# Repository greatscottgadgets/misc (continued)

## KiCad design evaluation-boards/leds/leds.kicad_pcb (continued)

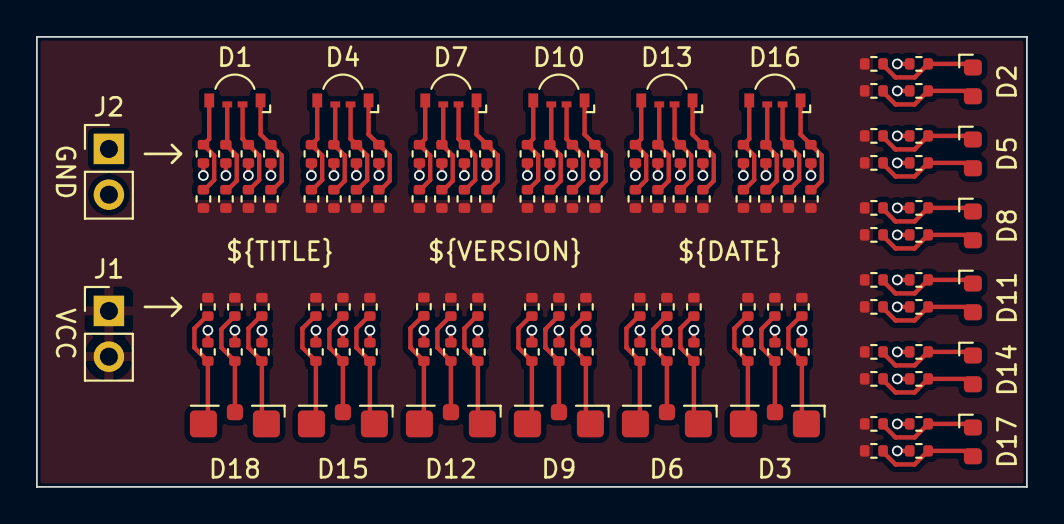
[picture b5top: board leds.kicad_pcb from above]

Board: 2 copper layers, 55.0 x 25.0 mm, 128 parts (0 on the bottom side), 56 nets.

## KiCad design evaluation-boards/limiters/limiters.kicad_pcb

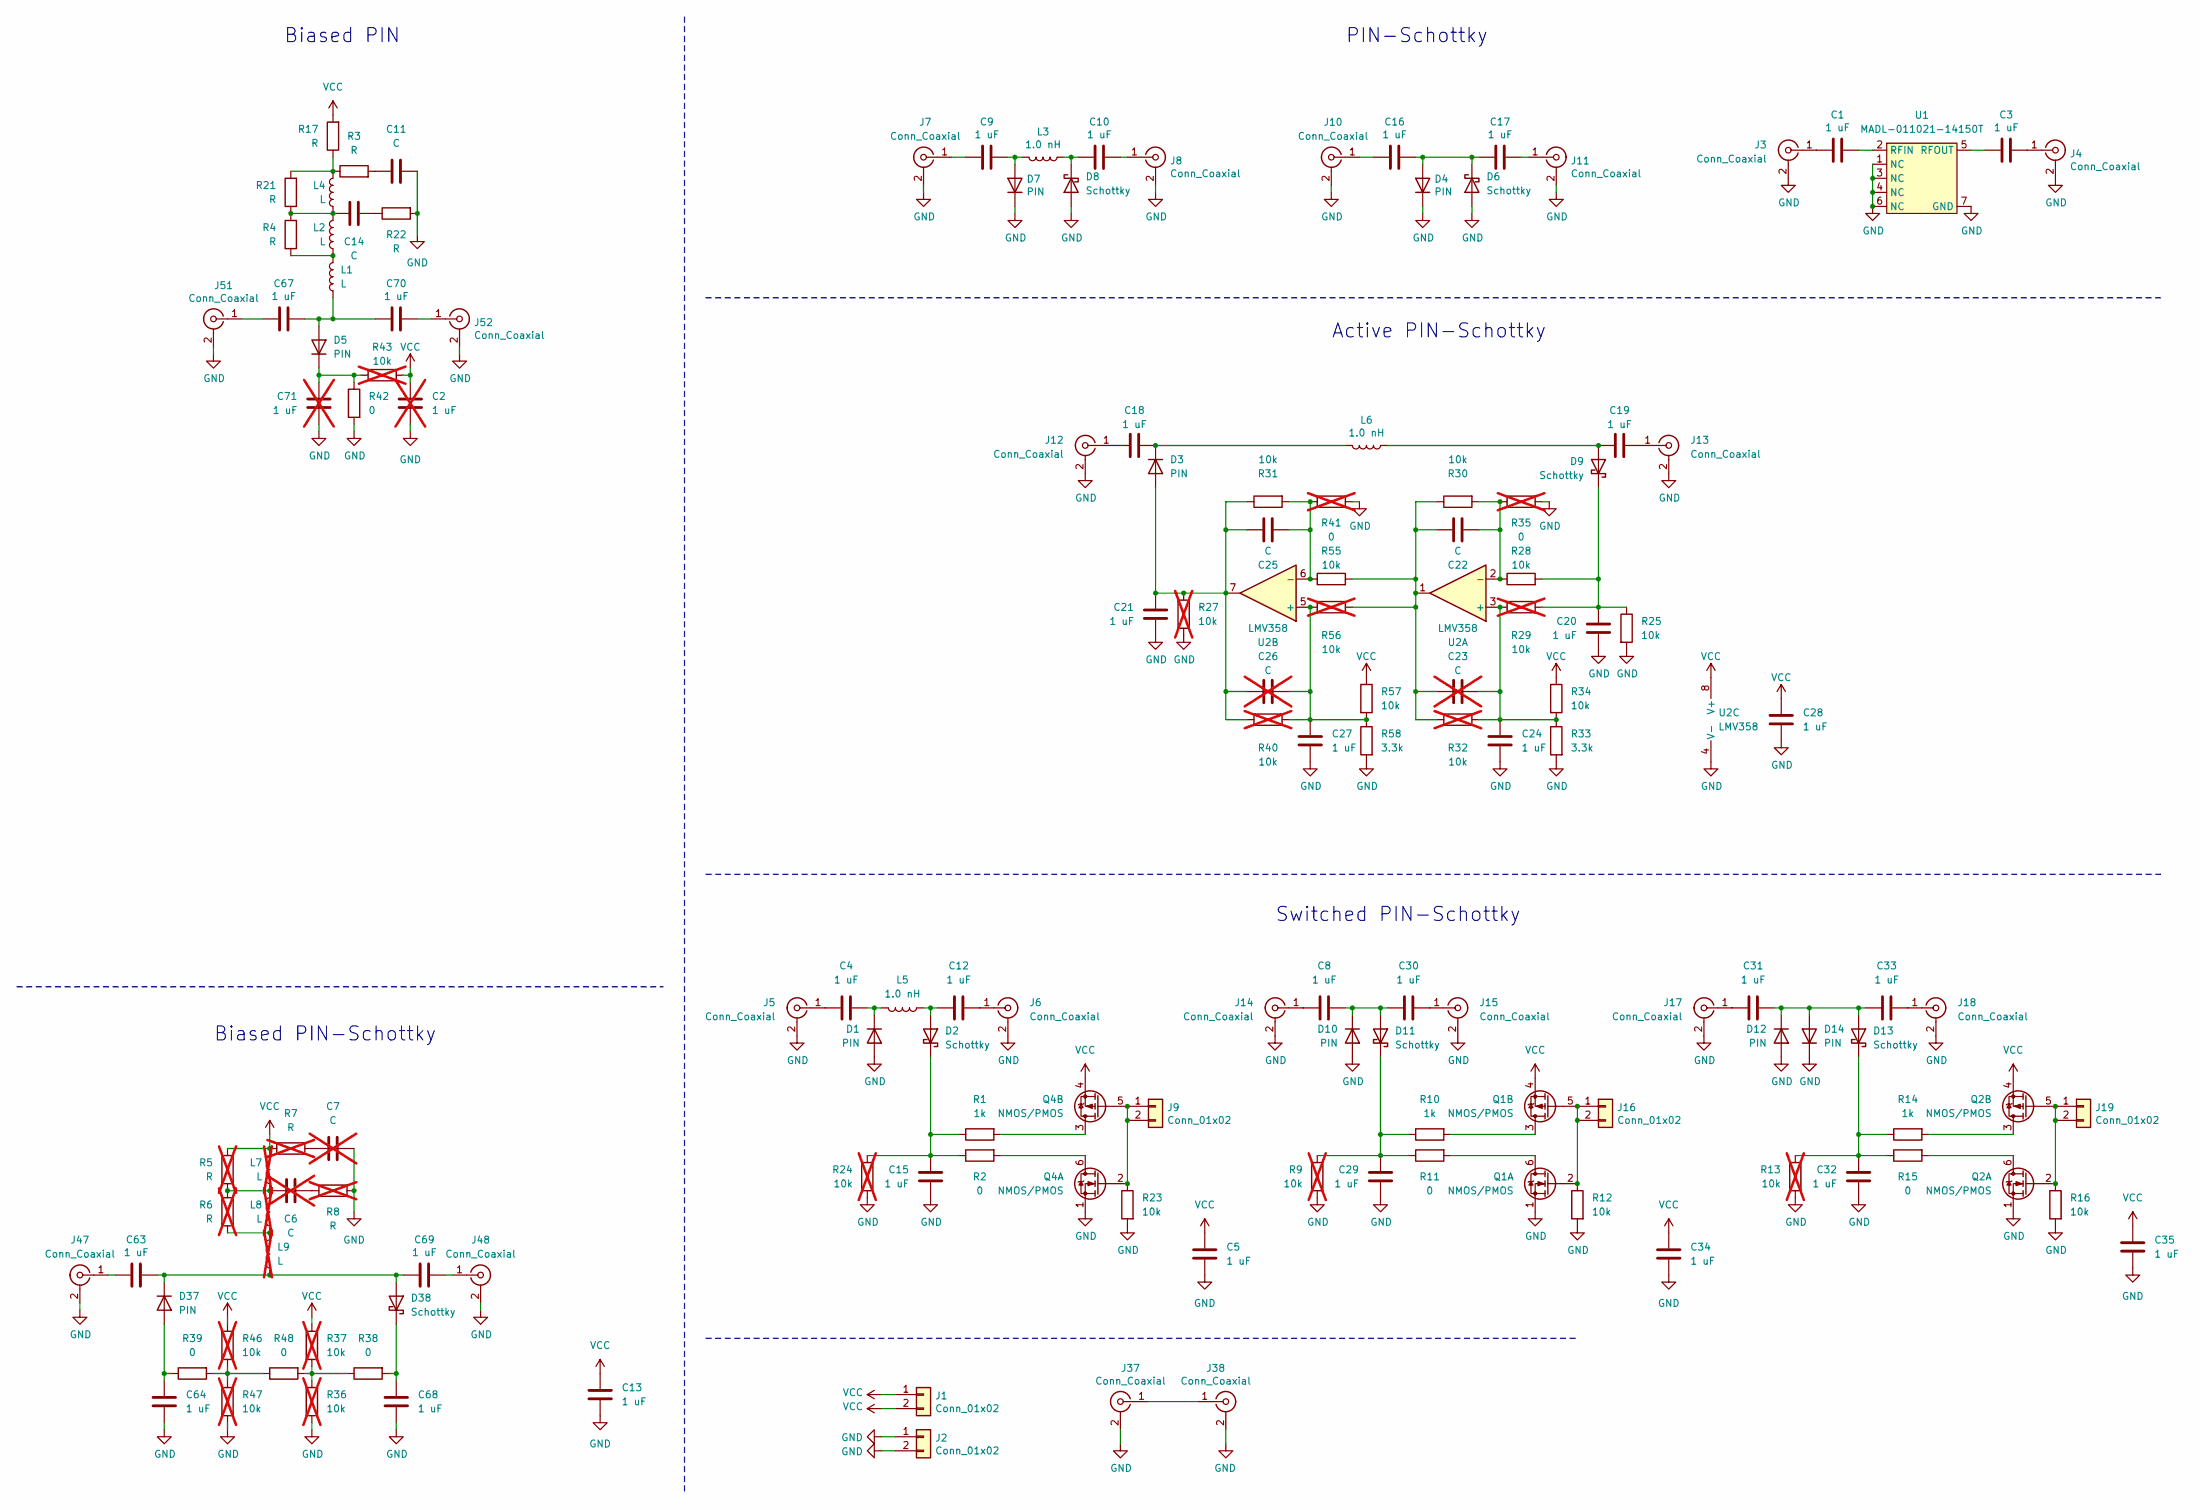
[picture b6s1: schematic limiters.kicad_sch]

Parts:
C1, C3, C5, C10, C12, C13, C15, C17, C18, C19, C20, C21, C24, C27, C28, C29, C30, C32, C33, C34, C35, C63, C64, C67, C68, C69, C70: 1 uF; C_0201_0603Metric; Part Number GRM033R61A105ME44D
C2, C71: 1 uF; C_0201_0603Metric; Part Number GRM033R61A105ME44D; not fitted
C4, C8, C31: 1 uF; C_0402_1005Metric; Part Number Capacitor_SMD:C_0402_1005Metric
C6, C7, C23, C26: C; C_0201_0603Metric; not fitted
C9, C16: 1 uF; C_0402_1005Metric
C11, C14, C22, C25: C; C_0201_0603Metric
D1, D3, D4, D5, D7, D10, D12, D14, D37: PIN; TSLP-2-19; Part Number BAR9002ELE6327XTMA1
D2, D6, D8, D9, D11, D13, D38: Schottky; TSSLP-2-1; Part Number BAT2402LSE6327XTSA1
J1, J2, J9, J16, J19: Conn_01x02; PinHeader_1x02_P2.54mm_Vertical
J3, J4, J5, J6, J7, J8, J10, J11, J12, J13, J14, J15, J17, J18, J37, J38, J47, J48, J51, J52: Conn_Coaxial; Linx_SMA_CONSMA003.062; Part Number CONSMA003.062
L1, L2: L; L_0201_0603Metric
L3, L5, L6: 1.0 nH; L_0201_0603Metric; Part Number LQP03HQ1N0W02D
L4: L; L_0805_2012Metric
L7: L; L_0805_2012Metric; not fitted
L8, L9: L; L_0201_0603Metric; not fitted
Q1, Q2, Q4: NMOS/PMOS; SOT-563; Part Number DMC2400UV
R1, R10, R14: 1k; R_0402_1005Metric
R2, R11, R15, R38, R39, R42, R48: 0; R_0402_1005Metric
R3, R4, R17, R21, R22: R; R_0201_0603Metric
R5, R6, R7, R8: R; R_0201_0603Metric; not fitted
R9, R13, R24, R27, R29, R32, R36, R37, R40, R43, R46, R47, R56: 10k; R_0402_1005Metric; not fitted
R12, R16, R23, R25, R28, R30, R31, R34, R55, R57: 10k; R_0402_1005Metric
R33, R58: 3.3k; R_0402_1005Metric
R35, R41: 0; R_0402_1005Metric; not fitted
U1: MADL-011021-14150T; TDFN-6-1EP_1.5x1.2mm_P0.4mm_EP0.47x0.8mm
U2: LMV358; MSOP-8_3x3mm_P0.65mm

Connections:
GND: C2.2, C5.2, C7.1, C11.1, C13.2, C15.2, C20.2, C21.2, C24.2, C27.2, C28.2, C29.2, C32.2, C34.2, C35.2, C64.2, C68.2, C71.2, D1.2 (A), D4.1 (K), D6.2 (A), D7.1 (K), D8.2 (A), D10.2 (A), D12.2 (A), D14.1 (K), J2.1, J2.2, J3.2 (Ext), J4.2 (Ext), J5.2 (Ext), J6.2 (Ext), J7.2 (Ext), J8.2 (Ext), J10.2 (Ext), J11.2 (Ext), J12.2 (Ext), J13.2 (Ext), J14.2 (Ext), J15.2 (Ext), J17.2 (Ext), J18.2 (Ext), J37.2 (Ext), J38.2 (Ext), J47.2 (Ext), J48.2 (Ext), J51.2 (Ext), J52.2 (Ext), Q1.1 (S), Q2.1 (S), Q4.1 (S), R8.2, R9.2, R12.2, R13.2, R16.2, R22.2, R23.2, R24.2, R25.2, R27.2, R33.2, R35.2, R36.2, R41.2, R42.2, R47.2, R58.2, U1.1 (NC), U1.3 (NC), U1.4 (NC), U1.6 (NC), U1.7 (GND), U2.4 (V-)
unnamed: C6.1, R8.1
unnamed: C6.2, L7.1, L8.2, R5.1, R6.2
unnamed: C7.2, R7.2
unnamed: C11.2, R3.2
unnamed: C14.1, R22.1
unnamed: C14.2, L2.2, L4.1, R4.2, R21.1
unnamed: C22.1, C23.1, R30.1, R32.1, R55.2, R56.2, U2.1
unnamed: C4.1, D1.1 (K), L5.2
unnamed: C12.2, D2.2 (A), L5.1
unnamed: C15.1, D2.1 (K), R1.1, R2.1, R24.1
unnamed: C21.1, C25.1, C26.1, D3.2 (A), R27.1, R31.1, R40.1, U2.7
unnamed: C18.1, D3.1 (K), L6.2
unnamed: C16.1, C17.2, D4.2 (A), D6.1 (K)
unnamed: C67.1, C70.2, D5.2 (A), L1.1
unnamed: C71.1, D5.1 (K), R42.1, R43.1
unnamed: C9.1, D7.2 (A), L3.2
unnamed: C10.2, D8.1 (K), L3.1
unnamed: C19.2, D9.2 (A), L6.1
unnamed: C20.1, D9.1 (K), R25.1, R28.2, R29.2
unnamed: C8.1, C30.2, D10.1 (K), D11.2 (A)
unnamed: C29.1, D11.1 (K), R9.1, R10.1, R11.1
unnamed: C31.1, C33.2, D12.1 (K), D13.2 (A), D14.2 (A)
unnamed: C32.1, D13.1 (K), R13.1, R14.1, R15.1
unnamed: C64.1, D37.2 (A), R39.1
unnamed: C63.1, C69.2, D37.1 (K), D38.2 (A), L9.1
unnamed: C68.1, D38.1 (K), R38.2
unnamed: C1.2, J3.1 (In)
unnamed: C3.1, J4.1 (In)
unnamed: C4.2, J5.1 (In)
unnamed: C12.1, J6.1 (In)
unnamed: C9.2, J7.1 (In)
unnamed: C10.1, J8.1 (In)
unnamed: J9.1, J9.2, Q4.2 (G), Q4.5 (G), R23.1
unnamed: C16.2, J10.1 (In)
unnamed: C17.1, J11.1 (In)
unnamed: C18.2, J12.1 (In)
unnamed: C19.1, J13.1 (In)
unnamed: C8.2, J14.1 (In)
unnamed: C30.1, J15.1 (In)
unnamed: J16.1, J16.2, Q1.2 (G), Q1.5 (G), R12.1
unnamed: C31.2, J17.1 (In)
unnamed: C33.1, J18.1 (In)
unnamed: J19.1, J19.2, Q2.2 (G), Q2.5 (G), R16.1
unnamed: J37.1 (In), J38.1 (In)
unnamed: C63.2, J47.1 (In)
unnamed: C69.1, J48.1 (In)
unnamed: C67.2, J51.1 (In)
unnamed: C70.1, J52.1 (In)
unnamed: L1.2, L2.1, R4.1
unnamed: L4.2, R3.1, R17.1, R21.2
unnamed: L8.1, L9.2, R6.1
unnamed: Q1.6 (D), R11.2
unnamed: Q1.3 (D), R10.2
unnamed: Q2.6 (D), R15.2
unnamed: Q2.3 (D), R14.2
unnamed: Q4.6 (D), R2.2
unnamed: Q4.3 (D), R1.2
unnamed: R36.1, R37.2, R38.1, R48.2
unnamed: R39.2, R46.2, R47.1, R48.1
unnamed: C1.1, U1.2 (RFIN)
unnamed: C3.2, U1.5 (RFOUT)
unnamed: C23.2, C24.1, R29.1, R32.2, R33.1, R34.2, U2.3 (+)
unnamed: C22.2, R28.1, R30.2, R35.1, U2.2 (-)
unnamed: C26.2, C27.1, R40.2, R56.1, R57.2, R58.1, U2.5 (+)
unnamed: C25.2, R31.2, R41.1, R55.1, U2.6 (-)
VCC: C2.1, C5.1, C13.1, C28.1, C34.1, C35.1, J1.1, J1.2, L7.2, Q1.4 (S), Q2.4 (S), Q4.4 (S), R5.2, R7.1, R17.2, R34.1, R37.1, R43.2, R46.1, R57.1, U2.8 (V+)

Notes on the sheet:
Active PIN-Schottky
Switched PIN-Schottky
Biased PIN-Schottky
PIN-Schottky
Biased PIN

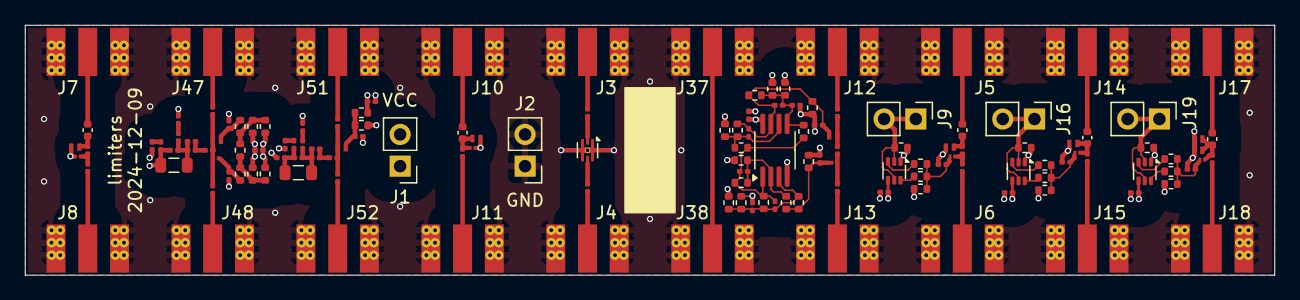
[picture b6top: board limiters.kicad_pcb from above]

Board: 4 copper layers, 100.0 x 20.0 mm, 143 parts (0 on the bottom side), 67 nets.

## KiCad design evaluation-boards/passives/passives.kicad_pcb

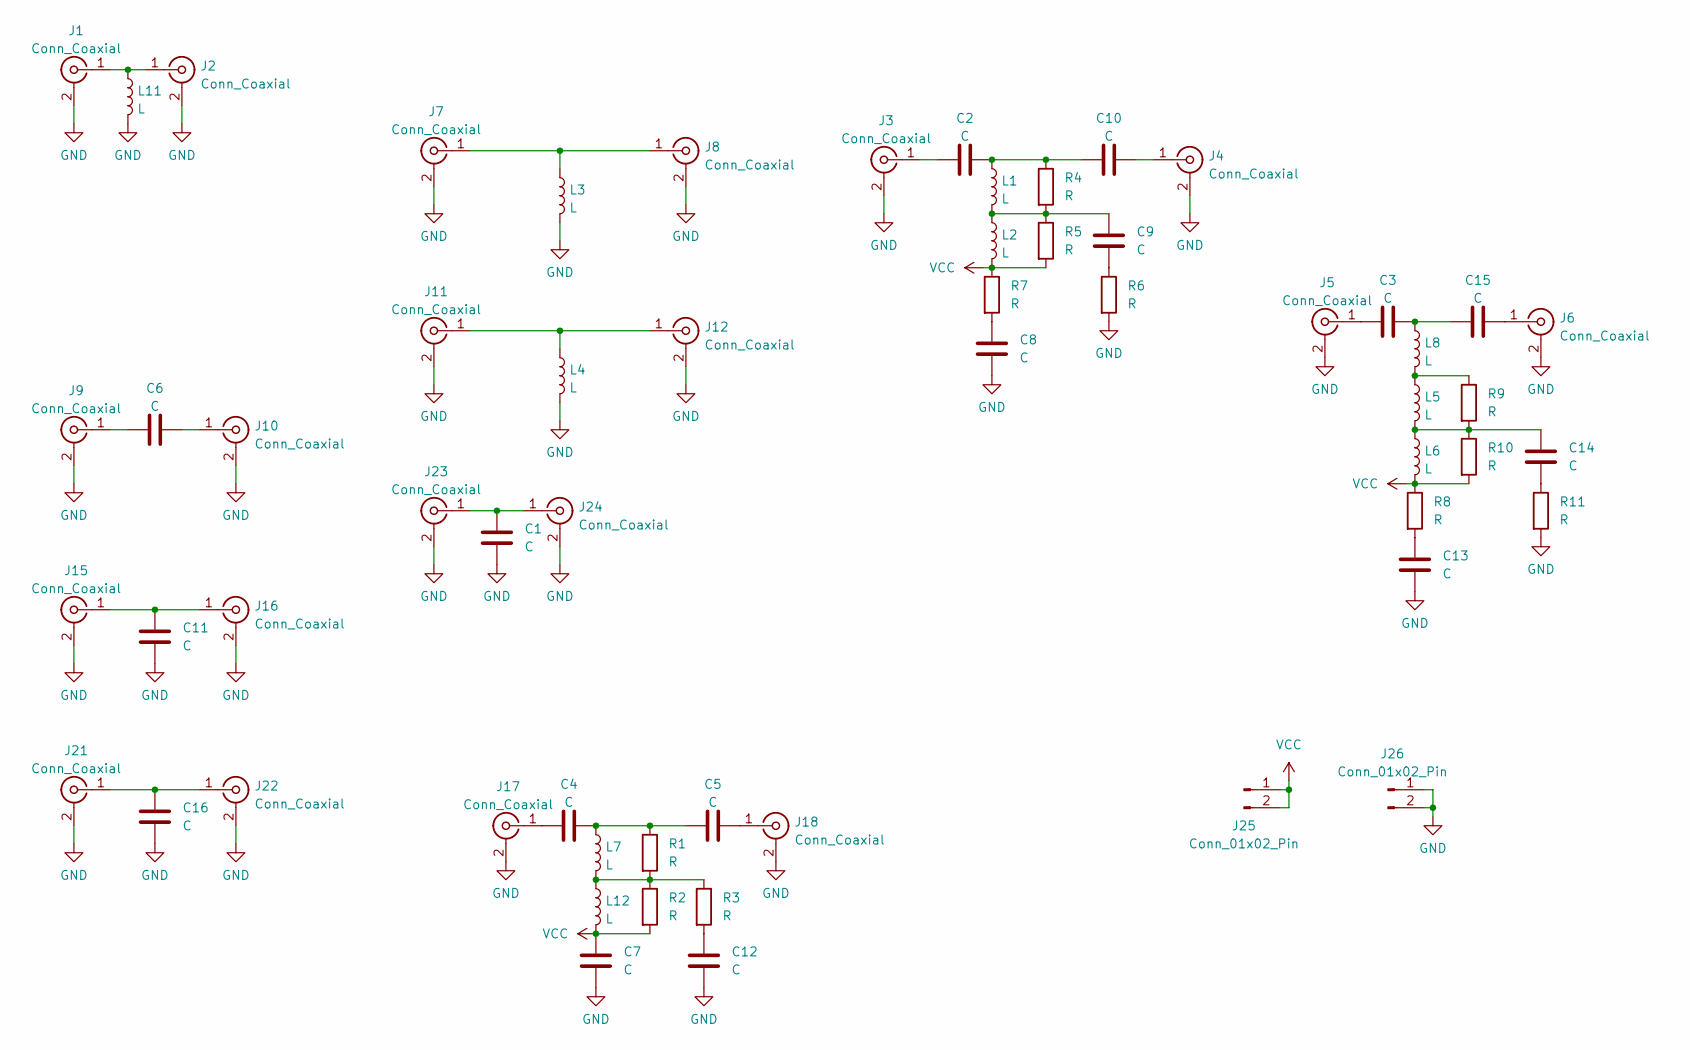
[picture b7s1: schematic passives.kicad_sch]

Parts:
C1, C2, C3, C4, C5, C8, C9, C10, C11, C13, C14, C15: C; C_0201_0603Metric
C6, C7, C12, C16: C; C_0402_1005Metric
J1, J2, J3, J4, J5, J6, J7, J8, J9, J10, J11, J12, J15, J16, J17, J18, J21, J22, J23, J24: Conn_Coaxial; Linx_SMA_CONSMA003.062
J25, J26: Conn_01x02_Pin; PinHeader_1x02_P2.54mm_Vertical
L1, L5, L8: L; L_0201_0603Metric
L2, L4, L6: L; L_0805_2012Metric
L3, L7, L11, L12: L; L_0603_1608Metric
R1, R2, R3: R; R_0402_1005Metric
R4, R5, R6, R7, R8, R9, R10, R11: R; R_0201_0603Metric

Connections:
GND: C1.1, C7.1, C8.1, C11.1, C12.1, C13.1, C16.1, J1.2 (Ext), J2.2 (Ext), J3.2 (Ext), J4.2 (Ext), J5.2 (Ext), J6.2 (Ext), J7.2 (Ext), J8.2 (Ext), J9.2 (Ext), J10.2 (Ext), J11.2 (Ext), J12.2 (Ext), J15.2 (Ext), J16.2 (Ext), J17.2 (Ext), J18.2 (Ext), J21.2 (Ext), J22.2 (Ext), J23.2 (Ext), J24.2 (Ext), J26.1, J26.2, L3.2, L4.2, L11.2, R6.2, R11.2
unnamed: C4.2, C5.1, L7.1, R1.1
unnamed: C8.2, R7.2
unnamed: C9.1, R6.1
unnamed: C9.2, L1.2, L2.1, R4.2, R5.1
unnamed: C2.2, C10.1, L1.1, R4.1
unnamed: C12.2, R3.2
unnamed: C13.2, R8.2
unnamed: C14.1, R11.1
unnamed: C14.2, L5.2, L6.1, R9.2, R10.1
unnamed: C3.2, C15.1, L8.1
unnamed: J1.1 (In), J2.1 (In), L11.1
unnamed: C2.1, J3.1 (In)
unnamed: C10.2, J4.1 (In)
unnamed: C3.1, J5.1 (In)
unnamed: C15.2, J6.1 (In)
unnamed: J7.1 (In), J8.1 (In), L3.1
unnamed: C6.1, J9.1 (In)
unnamed: C6.2, J10.1 (In)
unnamed: J11.1 (In), J12.1 (In), L4.1
unnamed: C11.2, J15.1 (In), J16.1 (In)
unnamed: C4.1, J17.1 (In)
unnamed: C5.2, J18.1 (In)
unnamed: C16.2, J21.1 (In), J22.1 (In)
unnamed: C1.2, J23.1 (In), J24.1 (In)
unnamed: L5.1, L8.2, R9.1
unnamed: L7.2, L12.1, R1.2, R2.1, R3.1
VCC: C7.2, J25.1, J25.2, L2.2, L6.2, L12.2, R2.2, R5.2, R7.1, R8.1, R10.2

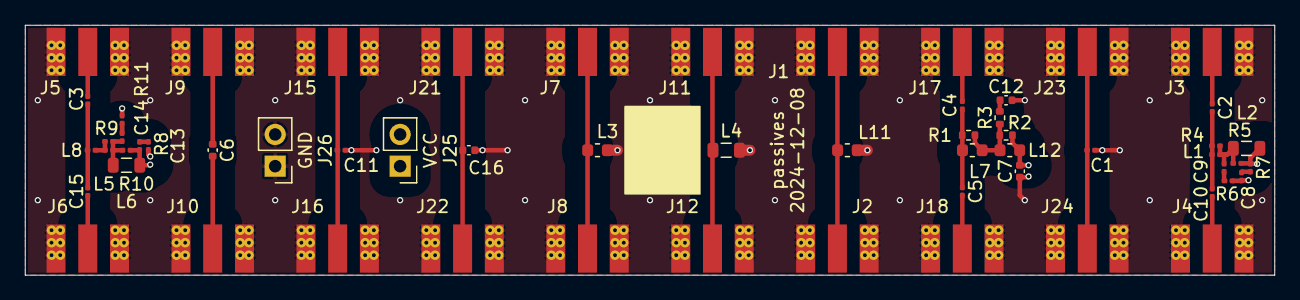
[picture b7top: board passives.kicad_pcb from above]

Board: 4 copper layers, 100.0 x 20.0 mm, 59 parts (0 on the bottom side), 28 nets.

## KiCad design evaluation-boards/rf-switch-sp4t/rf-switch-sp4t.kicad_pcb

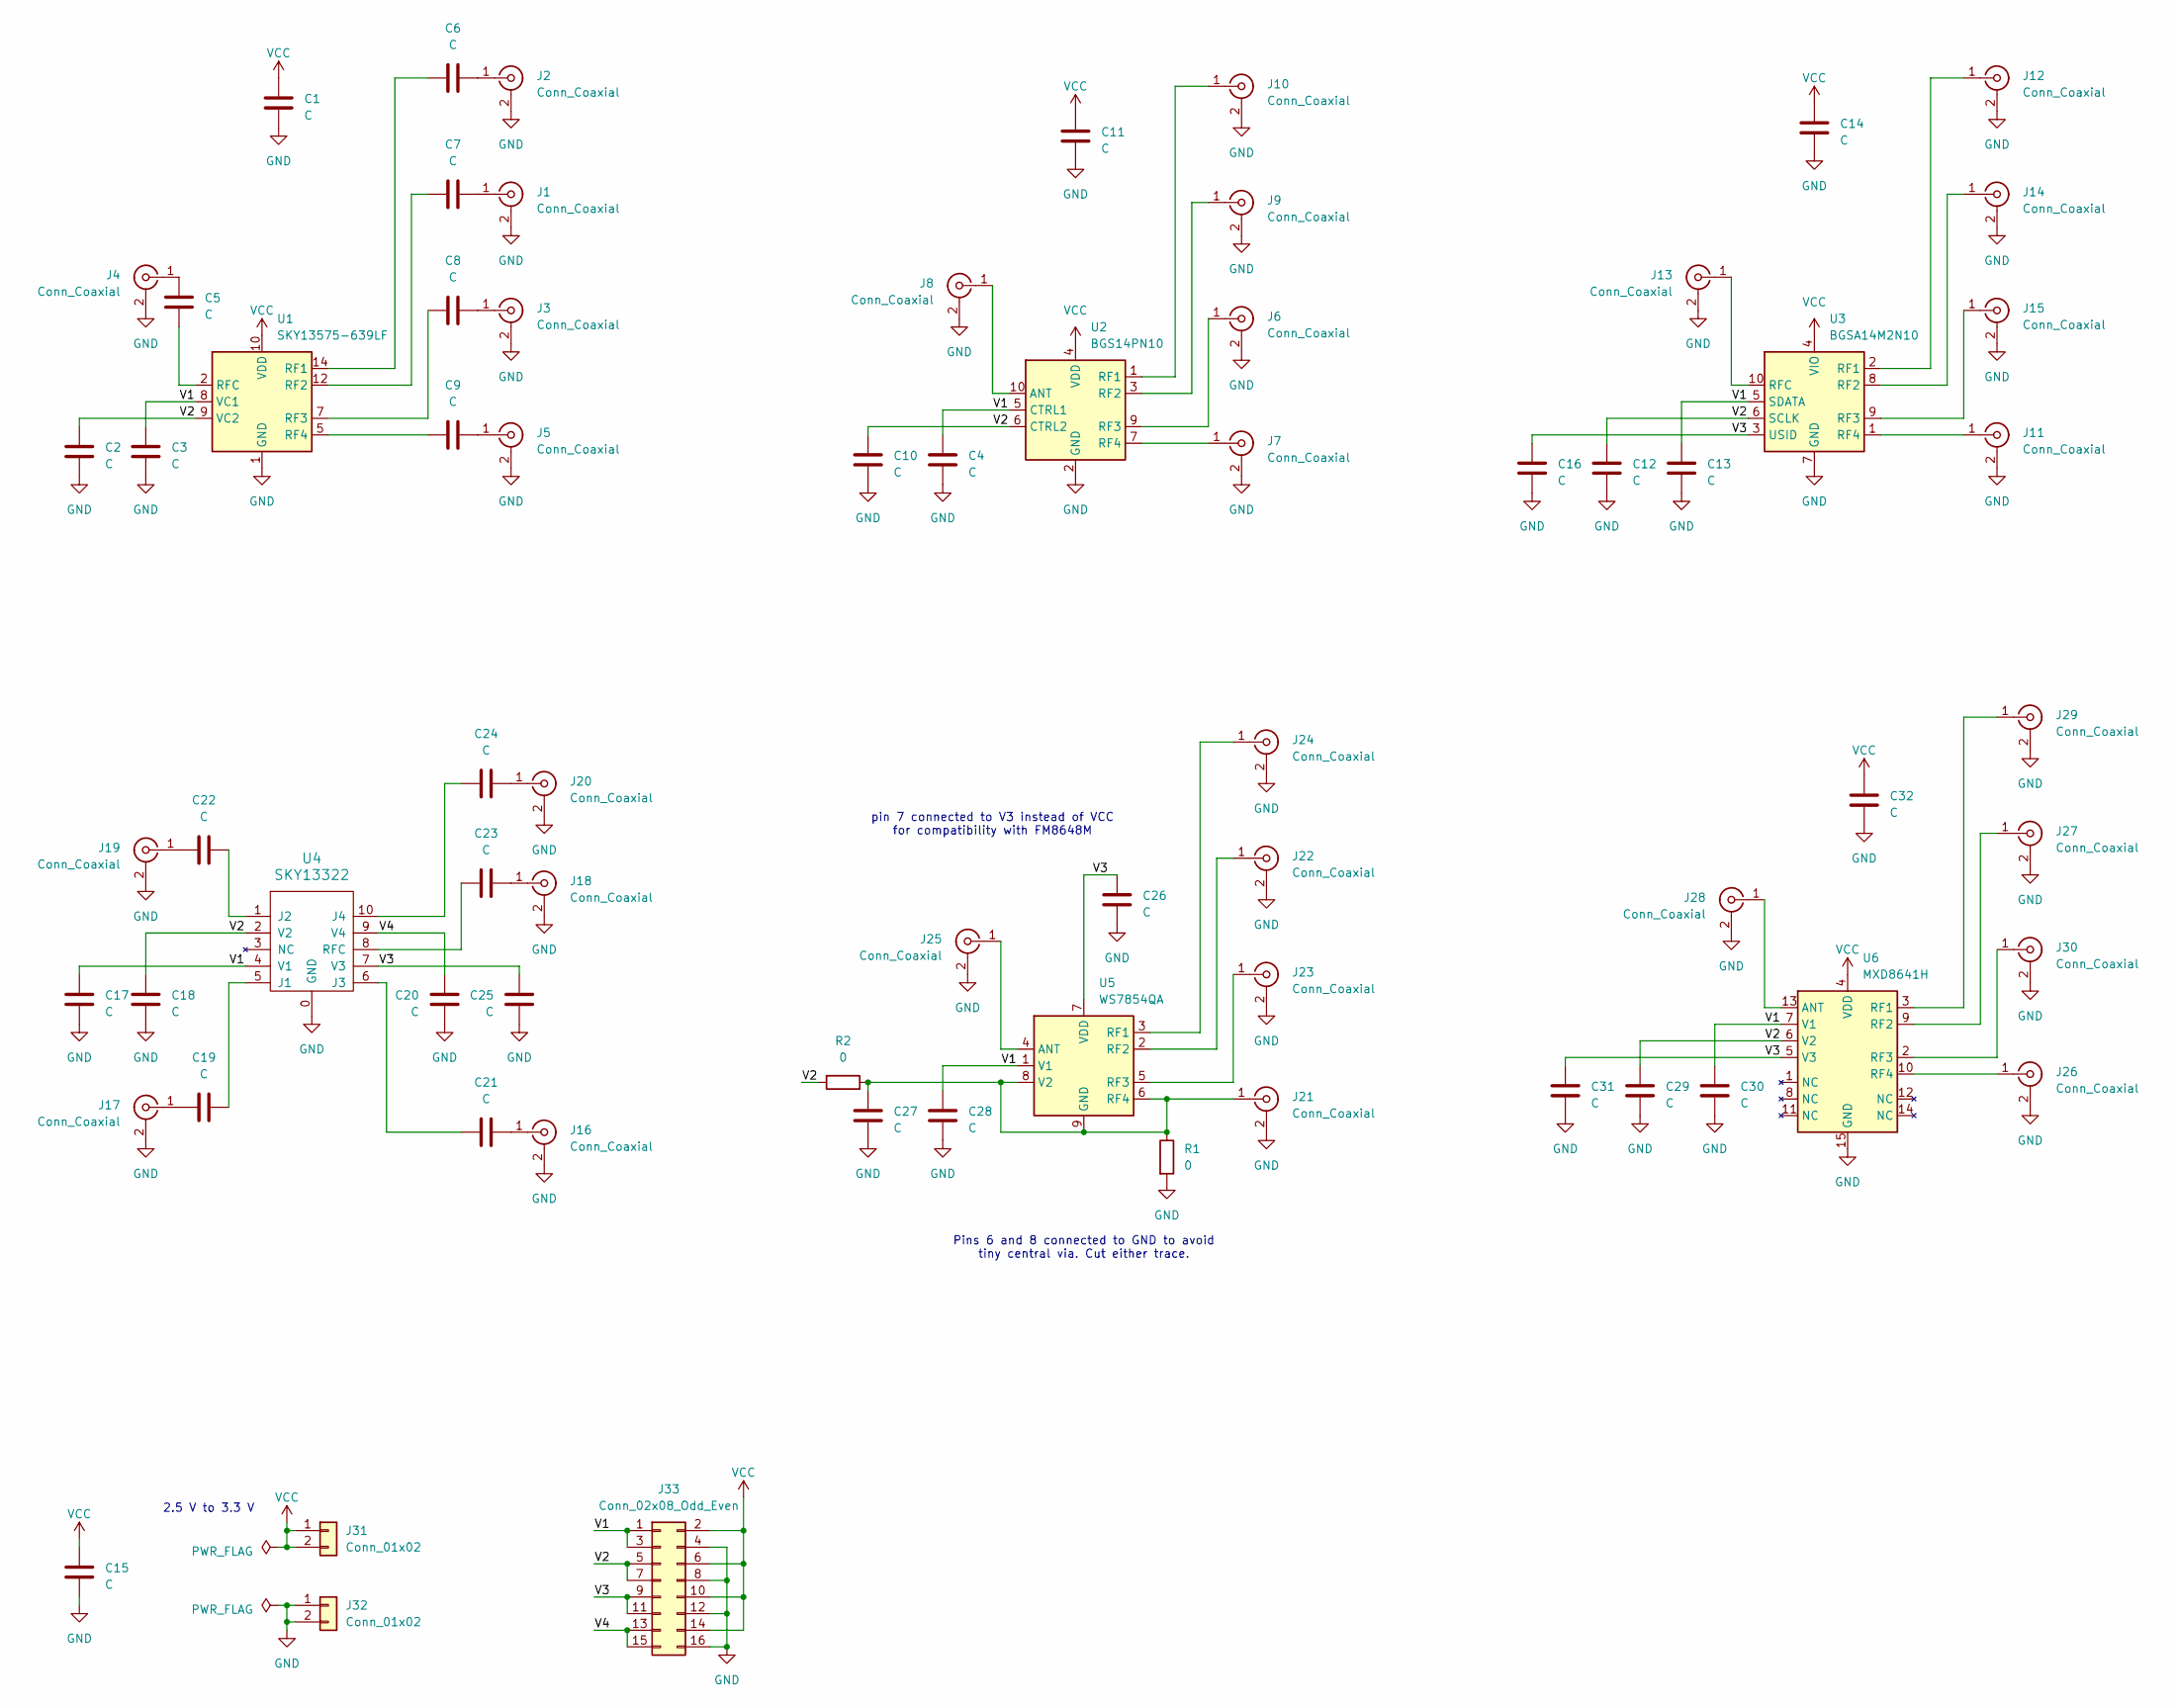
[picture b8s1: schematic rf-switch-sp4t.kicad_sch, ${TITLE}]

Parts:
C1, C2, C3, C4, C5, C6, C7, C8, C9, C10, C11, C12, C13, C14, C15, C16, C17, C18, C19, C20, C21, C22, C23, C24, C25, C26, C27, C28, C29, C30, C31, C32: C; C_0201_0603Metric
J1, J2, J3, J4, J5, J6, J7, J8, J9, J10, J11, J12, J13, J14, J15, J16, J17, J18, J19, J20, J21, J22, J23, J24, J25, J26, J27, J28, J29, J30: Conn_Coaxial; Linx_SMA_CONSMA003.062
J31, J32: Conn_01x02; PinHeader_1x02_P2.54mm_Vertical
J33: Conn_02x08_Odd_Even; PinHeader_2x08_P2.54mm_Vertical
R1, R2: 0; R_0201_0603Metric
U1: SKY13575-639LF; Skyworks_SKY13575_639LF
U2: BGS14PN10; ATSLP-10-50
U3: BGSA14M2N10; TSNP-10-10
U4: SKY13322; SKY13322-375LF
U5: WS7854QA; TSNP-9-3
U6: MXD8641H; SKY13414

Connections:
/V1: C3.1, C4.1, C13.1, C17.1, C28.1, C30.1, J33.1, J33.3, U1.8 (VC1), U2.5 (CTRL1), U3.5 (SDATA), U4.4 (V1), U5.1 (V1), U6.7 (V1)
/V2: C2.1, C10.1, C12.1, C18.1, C29.1, J33.5, J33.7, R2.1, U1.9 (VC2), U2.6 (CTRL2), U3.6 (SCLK), U4.2 (V2), U6.6 (V2)
/V3: C16.1, C25.1, C26.1, C31.1, J33.9, J33.11, U3.3 (USID), U4.7 (V3), U5.7 (VDD), U6.5 (V3)
/V4: C20.1, J33.13, J33.15, U4.9 (V4)
GND: C1.2, C2.2, C3.2, C4.2, C10.2, C11.2, C12.2, C13.2, C14.2, C15.2, C16.2, C17.2, C18.2, C20.2, C25.2, C26.2, C27.2, C28.2, C29.2, C30.2, C31.2, C32.2, J1.2 (Ext), J2.2 (Ext), J3.2 (Ext), J4.2 (Ext), J5.2 (Ext), J6.2 (Ext), J7.2 (Ext), J8.2 (Ext), J9.2 (Ext), J10.2 (Ext), J11.2 (Ext), J12.2 (Ext), J13.2 (Ext), J14.2 (Ext), J15.2 (Ext), J16.2 (Ext), J17.2 (Ext), J18.2 (Ext), J19.2 (Ext), J20.2 (Ext), J21.2 (Ext), J22.2 (Ext), J23.2 (Ext), J24.2 (Ext), J25.2 (Ext), J26.2 (Ext), J27.2 (Ext), J28.2 (Ext), J29.2 (Ext), J30.2 (Ext), J32.1, J32.2, J33.4, J33.8, J33.12, J33.16, R1.2, U1.1 (GND), U1.3 (GND), U1.4 (GND), U1.6 (GND), U1.11 (GND), U1.13 (GND), U1.15 (GND), U2.2 (GND), U2.8 (GND), U3.7 (GND), U4.0 (GND), U6.15 (GND)
unnamed: C7.2, J1.1 (In)
unnamed: C6.2, J2.1 (In)
unnamed: C8.2, J3.1 (In)
unnamed: C5.1, J4.1 (In)
unnamed: C9.2, J5.1 (In)
unnamed: J6.1 (In), U2.9 (RF3)
unnamed: J7.1 (In), U2.7 (RF4)
unnamed: J8.1 (In), U2.10 (ANT)
unnamed: J9.1 (In), U2.3 (RF2)
unnamed: J10.1 (In), U2.1 (RF1)
unnamed: J11.1 (In), U3.1 (RF4)
unnamed: J12.1 (In), U3.2 (RF1)
unnamed: J13.1 (In), U3.10 (RFC)
unnamed: J14.1 (In), U3.8 (RF2)
unnamed: J15.1 (In), U3.9 (RF3)
unnamed: C21.2, J16.1 (In)
unnamed: C19.1, J17.1 (In)
unnamed: C23.2, J18.1 (In)
unnamed: C22.2, J19.1 (In)
unnamed: C24.2, J20.1 (In)
unnamed: C27.1, J21.1 (In), R1.1, R2.2, U5.6 (RF4), U5.8 (V2), U5.9 (GND)
unnamed: J22.1 (In), U5.2 (RF2)
unnamed: J23.1 (In), U5.5 (RF3)
unnamed: J24.1 (In), U5.3 (RF1)
unnamed: J25.1 (In), U5.4 (ANT)
unnamed: J26.1 (In), U6.10 (RF4)
unnamed: J27.1 (In), U6.9 (RF2)
unnamed: J28.1 (In), U6.13 (ANT)
unnamed: J29.1 (In), U6.3 (RF1)
unnamed: J30.1 (In), U6.2 (RF3)
unnamed: C6.1, U1.14 (RF1)
unnamed: C7.1, U1.12 (RF2)
unnamed: C8.1, U1.7 (RF3)
unnamed: C9.1, U1.5 (RF4)
unnamed: C5.2, U1.2 (RFC)
unnamed: C19.2, U4.5 (J1)
unnamed: C22.1, U4.1 (J2)
unnamed: C21.1, U4.6 (J3)
unnamed: C24.1, U4.10 (J4)
unnamed: C23.1, U4.8 (RFC)
VCC: C1.1, C11.1, C14.1, C15.1, C32.1, J31.1, J31.2, J33.2, J33.6, J33.10, J33.14, U1.10 (VDD), U2.4 (VDD), U3.4 (VIO), U6.4 (VDD)

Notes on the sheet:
2.5 V to 3.3 V
pin 7 connected to V3 instead of VCC for compatibility with FM8648M
Pins 6 and 8 connected to GND to avoid tiny central via. Cut either trace.

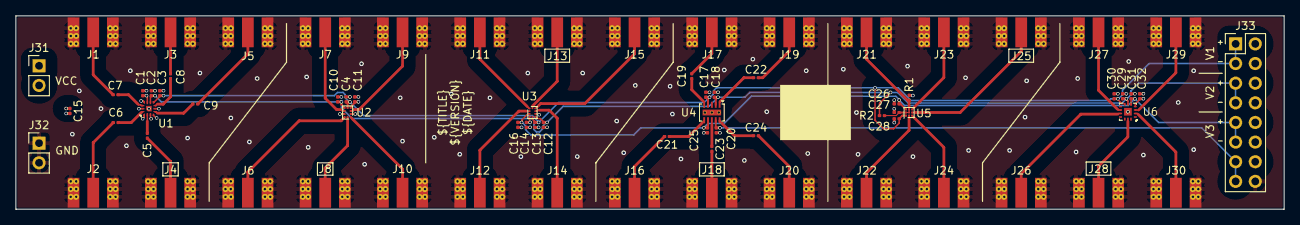
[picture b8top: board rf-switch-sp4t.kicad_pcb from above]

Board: 4 copper layers, 164.0 x 25.0 mm, 73 parts (0 on the bottom side), 46 nets.

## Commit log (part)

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2016-03-04 started evaluation boards, gsg-kicad-lib submodule
2016-03-05 started SKY13350 evaluation board
2016-03-06 finished SKY13350
2016-03-06 SKY13351 evaluation board
2016-09-26 SKY13411 evaluation board
2016-09-26 SKY13374 evaluation board
2020-08-12 add BGB741L7ESD evaluation board
2020-08-12 BGB741L7ESD: update with PCB edge SMA connectors
2021-02-22 add CC-test board for LUNA
2021-02-22 CC-test: change U2 and U3 to 74AUP2G126RA3-7
2022-03-23 add BGA622H6820 evaluation board
2022-03-23 add DC1722J5005AHF evaluation board
2022-03-23 add .gitignore for KiCad
2022-03-23 add quad balun directional coupler
2022-03-23 add trace width test board
2022-03-23 add filter test board
2022-03-23 update trace width test board
    - widen traces
    - use metric widths
    - revert to CONSMA003.062 footprint
    - add ground plane cutouts under SMA footprint
    The schematic wasn't updated as it is not very useful.
2022-04-07 add trace width layout for JLCPCB
2022-04-09 update trace width layout
2022-04-09 add limiters test board
2022-04-09 add ununs test board
2022-04-09 add passives test board
2022-08-11 add Si5351A board
2023-01-21 update trace width test board with SMA variants
2023-01-23 add pmos-or: FET-based alternative for diode-OR
2023-01-24 add vbus-switch board
2023-01-24 vbus-switch: up minimum trace/space to 3.5 mil
2023-01-24 vbus-switch: add part selections
2023-01-24 pmos-or: add part selections
2023-02-12 update vbus-switch
2023-02-13 vbus-switch: update resistor selection
2023-03-22 add SMA footprint test PCB for JLCPCB
2023-04-21 add rf-switch-dpdt board
2023-04-22 update CONSMA003.062 footprint
2023-04-22 add rf-switch-sp3t board
2023-04-22 add rf-switch-spdt board
2024-01-05 Update JLCPCB 7628 stack-up trace width board
    JLCPCB changed their stack-ups at some point in 2022. This board is
    intended to confirm the appropriate trace width for 50 ohm microstrip on
    their new 6-layer stack-up.
2024-11-04 Update trace width and SMA connector boards
2024-11-04 Update passives board
2024-11-04 Remove .kicad_prl file
2024-11-04 Rename BGB741L7ESD board to rf-amps
2024-11-04 Update rf-amps board
2024-11-05 Add more amplifiers to rf-amps board
2024-11-05 Update TSLP-7-1 footprint
2024-11-12 Update RF test boards
    - limiters
    - rf-switch-spdt
    - rf-switch-sp3t
2024-11-12 Add rf-switch-sp4t board
2024-11-12 Correct some library paths
2024-11-13 Update filter test board
2024-12-06 Update SMA connector board
2024-12-10 Update limiters board
2025-03-11 Update filters board
2025-03-12 Add leds board
2025-05-14 Add baluns board
2025-06-16 Update baluns board
